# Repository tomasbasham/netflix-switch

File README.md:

# Netflix-switch

An electronic schematic and PCB layout for a the lighting array of a Netflix Switch. This PCB is part of a tutorial series where I implement a version of the [original switch](http://makeit.netflix.com/the-switch) myself.

The tutorial series in is 3 parts, [parts 1](https://tomasbasham.co.uk/product%20design/2016/05/12/netflix-and-chill.html), [parts 2](https://tomasbasham.co.uk/product%20design/2016/05/15/netflix-and-chill-part-2.html), and [parts 3](https://tomasbasham.co.uk/product%20design/2016/06/10/netflix-and-chill-part-3.html) and goes through prototyping to assembling the switch using this PCB.

## Printing

The easiest possible way to get a copy of this board printed is to have a PCB fabrication house do it for you. I have had an amazing experience using [OSH Park](https://oshpark.com/) and highly recommend them. Simply upload the compressed gerber files to the website and they will print and ship them to you.

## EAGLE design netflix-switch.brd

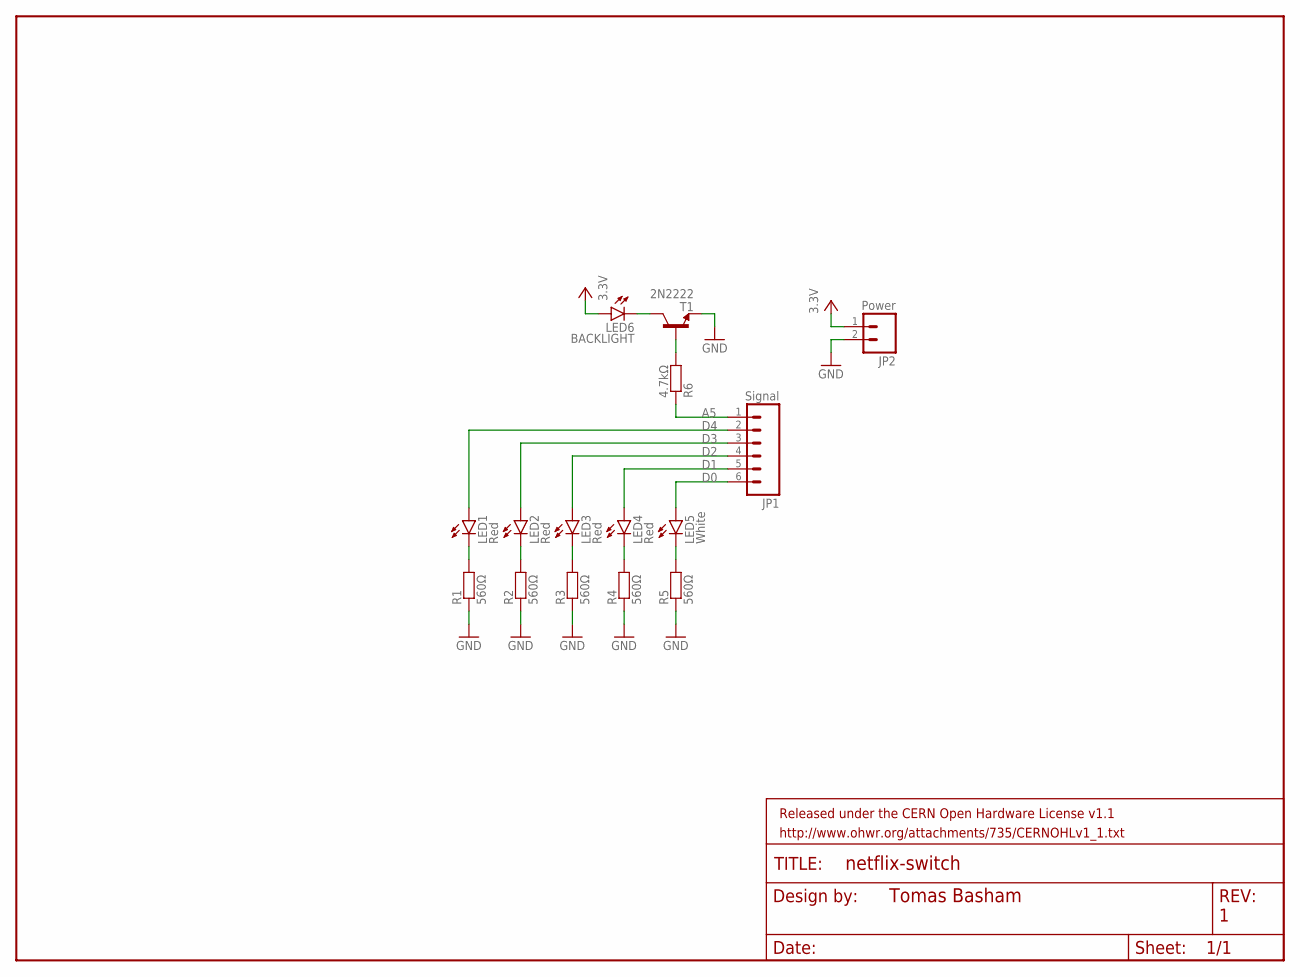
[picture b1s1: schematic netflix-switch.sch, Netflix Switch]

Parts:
FRAME1: FRAME-LETTER; CREATIVE_COMMONS
JP1: Signal; 1X06
JP2: Power; 1X02
LED1, LED2, LED3, LED4: Red; LED3MM-NS; MPN L-934ID-5V
LED5: White; LED3MM-NS; MPN VLHW4100
LED6: BACKLIGHT; LED5MM-NS
R1, R2, R3, R4, R5: 560Ω; 0603; MPN CRCW0603560RFKEA
R6: 4.7kΩ; 0603; MPN CRCW06034K70FKEA
T1: 2N2222; TO92-EBC-OVAL; MPN P2N2222AG

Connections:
A5: JP1.1, R6.1
D0: JP1.6, LED5.A
D1: JP1.5, LED4.A
D2: JP1.4, LED3.A
D3: JP1.3, LED2.A
D4: JP1.2, LED1.A
GND: JP2.2, R1.1, R2.1, R3.1, R4.1, R5.1, T1.E
unnamed: LED1.K (C), R1.2
unnamed: LED2.K (C), R2.2
unnamed: LED3.K (C), R3.2
unnamed: LED4.K (C), R4.2
unnamed: LED5.K (C), R5.2
unnamed: R6.2, T1.B
unnamed: LED6.K (C), T1.C
VCC: JP2.1, LED6.A

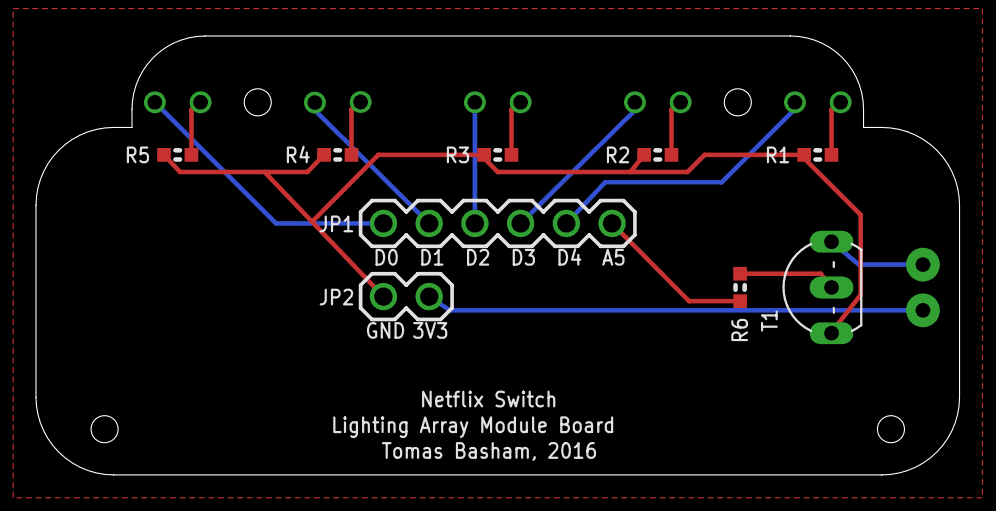
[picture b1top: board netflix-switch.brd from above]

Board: 2 copper layers, 51.3 x 24.4 mm, 16 parts (0 on the bottom side), 15 nets.

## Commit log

2016-09-26 Add Netflix Switch breakout board schematics, PCB design and bill of materials
2016-09-26 Add gerber files to be sent to a fabrication house
2016-09-26 Add rendered images

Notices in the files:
parts and their libraries:
falcon: Released under the CERN Open Hardware License v1.1
